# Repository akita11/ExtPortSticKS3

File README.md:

# ExtPort For StickS3

[M5Stack社のM5StickS3](https://www.switch-science.com/products/10921)の丈夫コネクタに接続して最大4つのGroveコネクタを増設し、複数のGrove接続のUNIT等を接続することができます。

## Groveコネクタのピン配置

4つのGroveコネクタのピン配置は以下のとおりです。
VDD（電源+5V）はM5StickS3から供給されます。
（※M5StickS3の仕様上、初期状態電はVDDが出力されず、ソフトウエアで有効にする必要があります）

- PortA（赤）: IO1/IO2/VDD/GND
- PortB（黒）: IO5/IO6/VDD/GND
- PortC（青）: IO7/IO8/VDD/GND
- PortD（緑）: IO43/IO44/VDD/GND

## Author

Junichi Akita (@akita11) / akita@ifdl.jp

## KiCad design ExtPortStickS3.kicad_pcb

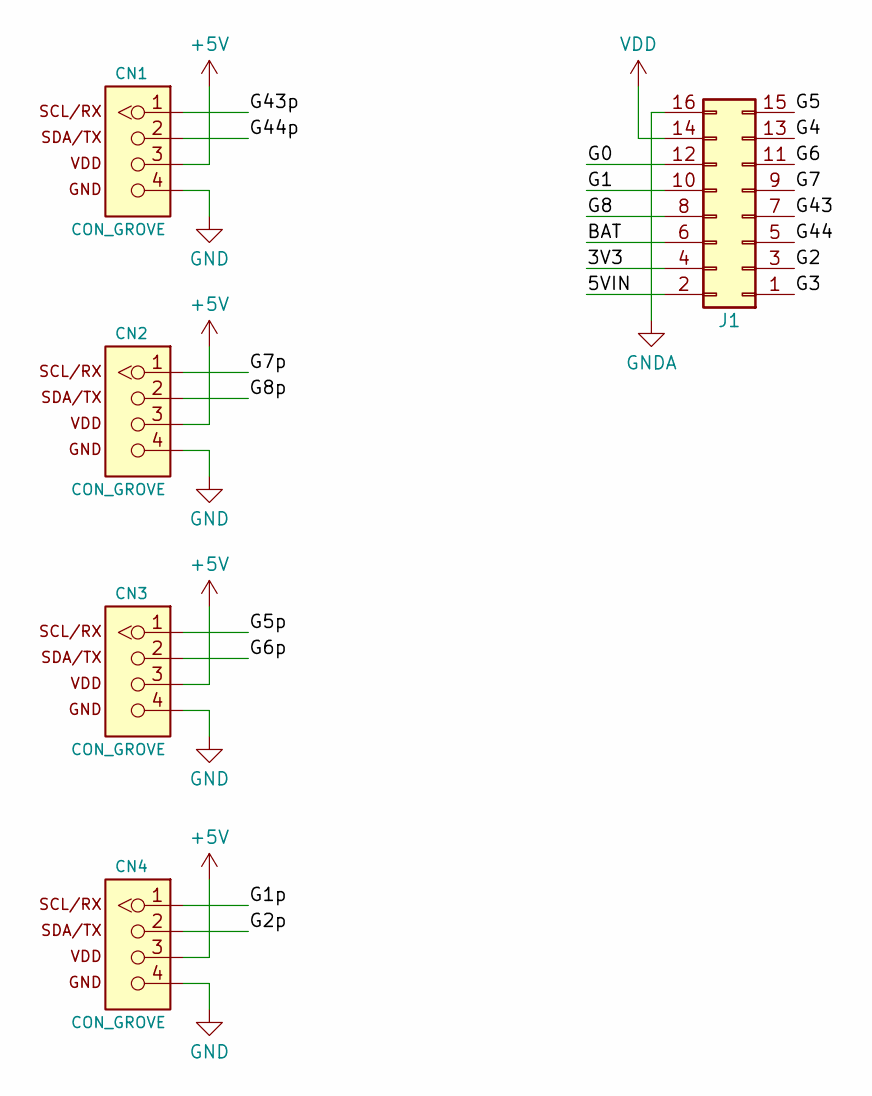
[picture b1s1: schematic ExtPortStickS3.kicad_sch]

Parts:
CN1, CN2, CN3, CN4: CON_GROVE; CON_GROVE_V_roundPad
J1: Conn_02x08_Odd_Even

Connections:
+5V: CN1.3, CN2.3, CN3.3, CN4.3
/3V3: J1.4
/5VIN: J1.2
/BAT: J1.6
/G0: J1.12
/G1: J1.10
/G1p: CN4.1
/G2: J1.3
/G2p: CN4.2
/G3: J1.1
/G4: J1.13
/G5: J1.15
/G5p: CN3.1
/G6: J1.11
/G6p: CN3.2
/G7: J1.9
/G7p: CN2.1
/G8: J1.8
/G8p: CN2.2
/G43: J1.7
/G43p: CN1.1
/G44: J1.5
/G44p: CN1.2
GND: CN1.4, CN2.4, CN3.4, CN4.4
GNDA: J1.16
VDD: J1.14

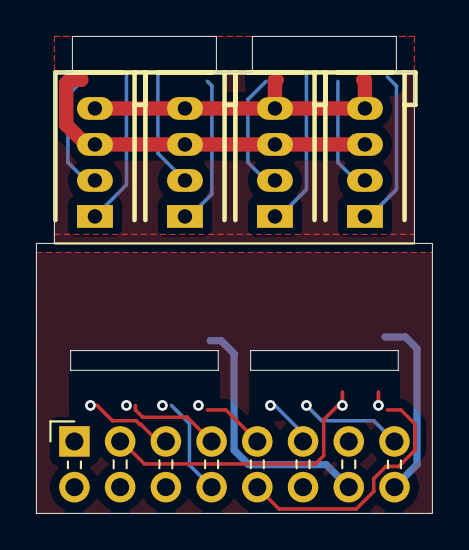
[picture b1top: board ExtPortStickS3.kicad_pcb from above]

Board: 2 copper layers, 22.0 x 26.5 mm, 5 parts (0 on the bottom side), 2 nets.

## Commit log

2026-03-30 add photo
